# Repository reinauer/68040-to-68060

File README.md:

# 68040-to-68060

This is a 68040 to 68060 adapter. It allows you to physically connect
a 68060 CPU to any CPU socket that fits a 68040 CPU, assuming there
is enough physical clearance.

## About

This work is a derivative of the 68040 to 68060 adapter
by richx which in turn is based on a 2013 design from
the a1k.org forum.

At the time of this writing, the original kicad project
can be found at https://eab.abime.net/showthread.php?t=100942

The differences between this design and the original KiCAD
version are:

  - Moved the inner 4-pin connector in line with the substrate
    and the pins of the PGA socket. This allows to use sockets
    with 5 rows of pins without using a dremel.
  - Move the capacitors a bit more to the center to make space
    for 5 pin row sockets.
  - use 0603 4.7k resistor networks instead of 0805 resistors to
    clean up the space and have fewer parts to solder
  - move all three diodes in line for easier soldering

## Assembly

The two PCBs need to be separated before assembly.

It is possible to build these with 0.1" pitch breakaway female
pin headers. However, is is much easier to solder full PGA sockets.
The top one has 206 pins, the bottom one 179. That is a large number
of breakaway pins if you go down that route.

'NOTE:' The bottom of the top PCBs has circles around some of the
pins. These are carrying VCC and must not make contact to the bottom
PCB or you will operate your 68060 at 5V instead of 3.3V. You might
destroy your processor this way, so be careful.

During assembly, you have the choice to either cut those pins, or you
can use an intermediate socket with those pins removed. This will increase
the height of your adapter by a few mm and increase the price because
you will need a third PGA socket, but make the assembly process a lot
cleaner and more reproducible.

Further reading on my adventures building these:
* [68040 to 68060 – Upformation](https://amiga.technology/2021/01/18/68040-to-68060-upformation/)
* [Finding common GND](https://amiga.technology/2021/02/25/finding-common-gnd/)
* [All good things](https://amiga.technology/2021/03/21/all-good-things/)

## Bill of Materials

Here's the [Bill of Materials (BOM)](https://htmlpreview.github.io/?https://raw.githubusercontent.com/reinauer/68040-to-68060/main/bom.html).

## Make your own

* [PCBWay](https://www.pcbway.com/project/shareproject/68040_to_68060_adapter.html)
* [OSHpark](https://oshpark.com/shared_projects/q8HjYPrh)

## Credits

Big thank you goes to richx, who did the original KiCAD version
and to Mozart, Lemmy and Matze from the a1k.org forum for the
Eagle version before that.

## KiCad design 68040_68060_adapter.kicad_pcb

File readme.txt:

A KiCAD respin of the 040-060-Adapter_mk2a Eagle project from a few years ago. Size of bottom PCB minimized for 
better fit, top/bottom PCBs combined into single multi-design, voltage regulator moved to top PCB and a couple of
other features.

I built the NO-DIODES PCB version only to later realize that the 68060 User's Manual recommends three diodes in series
(section 11.2.1.2) after people mentioned the diodes in different forum. I hacked/soldered three regular sized diodes
in series directly to the VCC and 3V3 pins on the voltage regulator but amended the KiCAD design and added the three
diodes in series. I never built this newer version, but if I was to attempt this again, it would be with the newer PCB
version with the diodes.

I ordered a thinner 1mm (vs standard 1.6mm) PCB for more access to thicker part of socket pins. The top PCB marks
the pins with circles that need to be cut. Care has to be taken to prevent the marked 040 pins on the bottom PCB from
contacting the 060 pins on the top PCB. Worst case 5V goes to 060 3.3V pins. It was not enough to just cut the circled
pins, I also popped out the corresponding pins from the 040 socket, cut them right above the ferrule and put them back
in. Because the cut pins on the 040 socket are now technically damaged, it's mainly the solder on the underside of these
pins that are keeping them from pushing up onto the 060 pins when inserted into CPU socket, so I measured resistance
from VCC to 3V3 after install to make sure there were no short circuits.

I used real 040 and 060 sockets. There is not much room between the pins for the soldering iron. I had to use a thicker
chisel soldering tip at higher temperature to allow enough heat for the solder to wick to the thin pin solder pads. A
lot of the pads are connected to the ground or power planes that act as big heatsinks sucking away the heat, causing
solder to only stick to the pins instead of also to the solder pads. Both top and bottom PCBs should be carefully
inspected to make sure the solder has actually wicked to the solder pads, and that there are no shorts and no excessive
solder on pins. Might be easier to just use cheap socket strips instead of real sockets. The strips could be soldered
row by row (with CPU or other strips inserted to keep them straight) which would allow much better access for the
soldering iron tip.

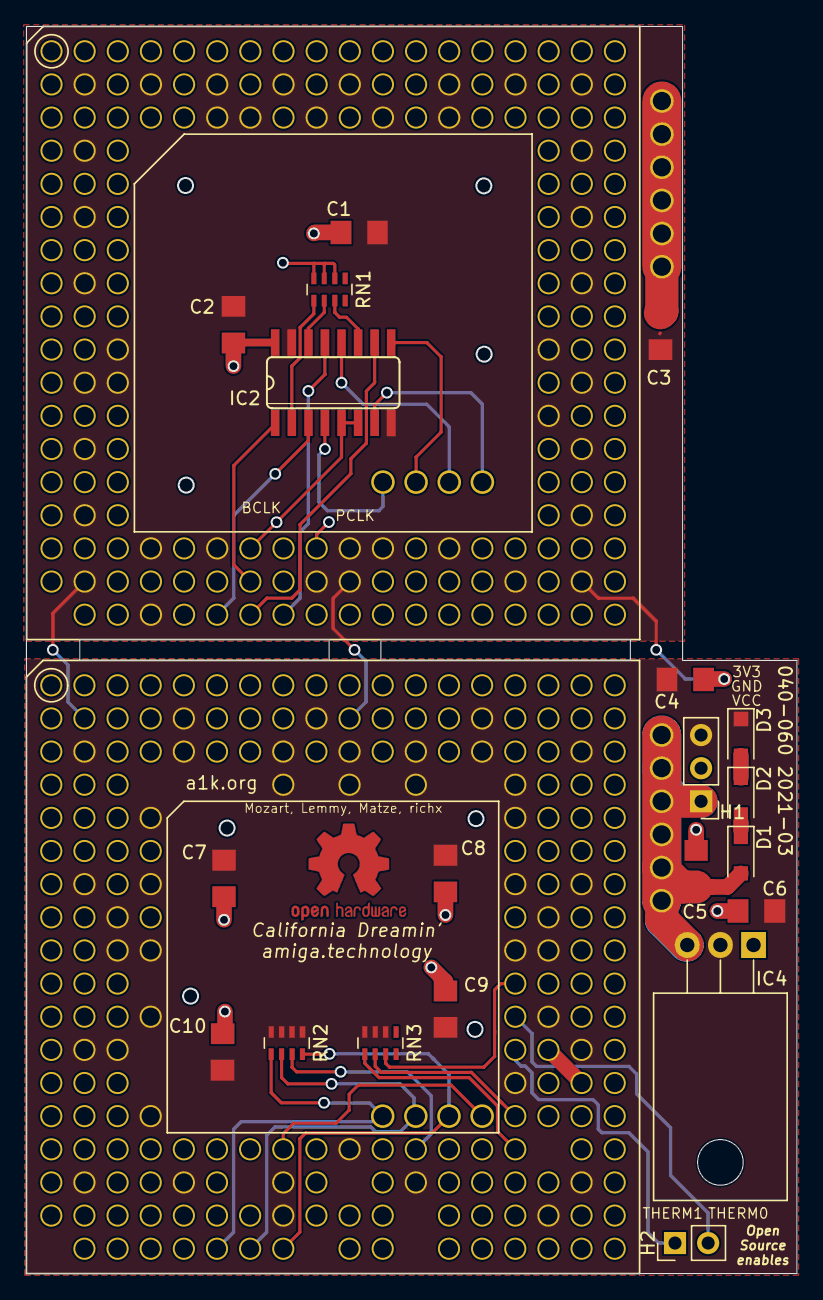
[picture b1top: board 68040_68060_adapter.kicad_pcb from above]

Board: 2 copper layers, 59.1 x 95.6 mm, 26 parts (0 on the bottom side), 28 nets.

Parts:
C1, C4: 10u; C1206
C2, C3, C5, C6, C7, C8, C9, C10: 100n; C1206
D1, D2, D3: 1N4001; D_SOD-123F
H1: Power; PinHeader_1x03_P2.54mm_Vertical
H2: Therm; PinHeader_1x02_P2.54mm_Vertical
IC1: PGA179_BIG
IC2: 74F257; SO16
IC3: MC68060RCPGA_BIG; PGA206_BIG
IC4: LMS1585-3.3; TO-220-3_Horizontal_TabDown
RN1: 4.7K; R_Array_Concave_4x0603
RN2, RN3: 4.7k; R_Array_Concave_4x0603
U4$1, U4$1#2: 4POL; 4-PIN-1.4HOLES
U6$1, U6$1#2: 6POL; 6-PIN-1.4HOLES

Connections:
40_BCLK: IC1.R07, IC2.5, IC2.6
40_IPL0: IC1.T08, IC2.13
40_IPL1: IC1.T07, IC2.10
40_IPL2: IC1.T06, IC2.3
40_RSTI: IC1.S07, IC2.1
60_CLKEN: IC2.7, U4$1.P4$1
60_IPL0: IC2.12, U4$1.P4$2
60_IPL1: IC2.9, U4$1.P4$3
60_IPL2: IC2.4, U4$1.P4$4
+3V3: C4.1, C6.1, C7.1, C8.1, C9.1, C10.1, D3.1, H1.3, IC3.B05, IC3.B09, IC3.B14, IC3.C02, IC3.C05, IC3.C08, IC3.C10, IC3.C12, IC3.C14, IC3.C17, IC3.D08, IC3.D10, IC3.D12, IC3.D15, IC3.E04, IC3.E15, IC3.G02, IC3.G04, IC3.G15, IC3.G17, IC3.H03, IC3.H16, IC3.J03, IC3.J04, IC3.J15, IC3.J16, IC3.L04, IC3.L16, IC3.M02, IC3.M03, IC3.M17, IC3.N15, IC3.P04, IC3.Q10, IC3.R02, IC3.R05, IC3.R08, IC3.R12, IC3.R17, IC3.S08, IC3.S16, IC4.2, RN2.1, RN2.2, RN2.3, RN2.4, RN3.2, RN3.3, RN3.4
BTT: IC3.Q15, RN3.5
CLA: IC3.K15, RN3.7
CLKEN: IC3.Q08, U4$1#2.P4$1
GND: C1.2, C2.2, C3.2, C4.2, C5.2, C6.2, C7.2, C8.2, C9.2, C10.2, H1.2, IC1.B02, IC1.B04, IC1.B06, IC1.B08, IC1.B10, IC1.B13, IC1.B15, IC1.B17, IC1.C06, IC1.C07, IC1.C09, IC1.C11, IC1.C13, IC1.D02, IC1.D17, IC1.F02, IC1.F17, IC1.H02, IC1.H17, IC1.K03, IC1.K16, IC1.L02, IC1.L03, IC1.L17, IC1.M16, IC1.N02, IC1.N17, IC1.Q02, IC1.Q17, IC1.R04, IC1.R06, IC1.R10, IC1.R11, IC1.R13, IC1.S02, IC1.S09, IC1.S10, IC1.S15, IC1.S17, IC1.T04, IC2.8, IC2.15, IC3.B02, IC3.B04, IC3.B06, IC3.B08, IC3.B10, IC3.B13, IC3.B15, IC3.B17, IC3.C06, IC3.C07, IC3.C09, IC3.C11, IC3.C13, IC3.D02, IC3.D17, IC3.F02, IC3.F04, IC3.F15, IC3.F17, IC3.H02, IC3.H04, IC3.H15, IC3.H17, IC3.K03, IC3.K16, IC3.L02, IC3.L03, IC3.L17, IC3.M16, IC3.N02, IC3.N17, IC3.Q02, IC3.Q09, IC3.Q11, IC3.Q17, IC3.R04, IC3.R06, IC3.R11, IC3.R13, IC3.S02, IC3.S09, IC3.S10, IC3.S15, IC3.S17, IC4.1
IPL0: IC3.T08, RN2.8, U4$1#2.P4$2
IPL1: IC3.T07, RN2.6, U4$1#2.P4$3
IPL2: IC3.T06, RN2.5, U4$1#2.P4$4
unnamed: IC2.2, RN1.5
unnamed: IC2.11, RN1.7
unnamed: IC2.14, RN1.6
ND1: D1.1, D2.2
ND2: D2.1, D3.2
SNOOP: IC3.P15, RN3.6
THERM0: H2.2, IC3.L15
THERM1: H2.1, IC3.M15
TRA: IC3.Q12, RN2.7
VCC: C1.1, C2.1, C3.1, IC1.B05, IC1.B09, IC1.B14, IC1.C02, IC1.C05, IC1.C08, IC1.C10, IC1.C12, IC1.C14, IC1.C17, IC1.G02, IC1.G17, IC1.H03, IC1.H16, IC1.J03, IC1.J16, IC1.L16, IC1.M02, IC1.M03, IC1.M17, IC1.R02, IC1.R05, IC1.R08, IC1.R12, IC1.R17, IC1.S08, IC1.S16, IC2.16, RN1.2, RN1.3, RN1.4, U6$1#2.P6$1, U6$1#2.P6$2, U6$1#2.P6$3, U6$1#2.P6$4, U6$1#2.P6$5, U6$1#2.P6$6
VCC2: C5.1, D1.2, H1.1, IC4.3, U6$1.P6$1, U6$1.P6$2, U6$1.P6$3, U6$1.P6$4, U6$1.P6$5, U6$1.P6$6

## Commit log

2021-03-14 Original version from richx
    https://eab.abime.net/showthread.php?t=100942
2021-03-14 Original version by richx
    https://eab.abime.net/showthread.php?t=100942
2021-03-14 Updated version 03-2021
    - move inner connector in line with substrate
    and the pins of the socket. This allows to use sockets
    with 5 rows of pins without using a dremel
    - move capacitors a bit more to the center to make space
    for 5 pin row sockets.
    - use 0603 4.7k resistor networks instead of 0805 resistors
2021-03-16 Add interactive BOM and update README
    Made a BOM with https://github.com/openscopeproject/InteractiveHtmlBom
    and improved the README based on feedback.
2021-03-16 Fix BOM link
    Using htmlpreview.github.io is the way to go.
2021-07-09 Properly connect IPL2
2021-07-20 Add third part of the blog documentation
